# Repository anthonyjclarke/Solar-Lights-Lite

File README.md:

# Solar Lights Lite

Solar Lights Lite is a modular, low-power solar lighting system you build
yourself from common hobby modules. A small panel charges a protected Li-ion
battery; an ATmega328P controller sleeps most of the time, detects dusk with a
light sensor, and runs a **low-power LED string** from dusk to dawn. An
optional Wemos D1 Mini reports everything to Home Assistant.

It is also a learning project. Each module – power, controller, lighting,
sensor, telemetry – is built and tested on its own, so along the way you
practise soldering and SMD rework, read datasheets, program an AVR over ISP,
write low-power embedded C++, parse a serial protocol in ESPHome, and build
Home Assistant dashboards and automations.

---

## Low-power lights only

The controller drives the LED string **directly by PWM from pin D9** through a
56 Ω resistor. There is no driver transistor, so the whole string must run at
20 mA or less from a 3–4.2 V supply. Small low-power LED strings are ideal;
mains lights, 12 V garden lights and conventional or legacy fittings cannot be
used. The resistor sets the current and PWM sets the brightness. Brighter
lighting needs a driver stage: see [Going further](docs/12-going-further.md).

---

## System at a glance

```mermaid
flowchart LR
    PV[Solar panel] --> CHG[Protected Li-ion charger]
    CHG --> BAT[1S2P 18650 battery]
    CHG --> MCU[ATmega328P controller]
    MCU --> LDR[Light sensor]
    MCU -- PWM --> LED[Low-power LED string]
    MCU -. serial .-> D1[D1 Mini telemetry]
    D1 -. Wi-Fi .-> HA[Home Assistant]
```

| Module | What it does                       | Build guide                               |
| :----- | :--------------------------------- | :---------------------------------------- |
| A      | Panel, charger, fused 1S2P battery | [Power](docs/03-build-power.md)           |
| B      | ATmega328P controller at 8 MHz     | [Controller](docs/04-build-controller.md) |
| C      | Low-power LED string on D9         | [Lighting](docs/05-build-lighting.md)     |
| D      | Light sensor and test button       | [Sensor](docs/06-build-sensor.md)         |
| E      | D1 Mini telemetry (optional)       | [Telemetry](docs/07-build-telemetry.md)   |
| F      | Enclosure and final assembly       | [Commissioning](docs/10-commissioning.md) |

### Telemetry tiers

| Tier | Name                 | Role                               |
| :--- | :------------------- | :--------------------------------- |
| 0    | Standalone           | Lights only, no Wi-Fi              |
| 1    | Advanced Telemetry   | Always-on commissioning instrument |
| 2    | Production Telemetry | Hourly battery-powered reporting   |

**Advanced Telemetry is the road to a finished installation.** While you build,
calibrate and soak-test, it shows every decision the controller makes in Home
Assistant. When the system passes its acceptance gates, you reflash both boards
and move the D1 Mini to battery power for low-power production reporting. The
wiring stays the same.

---

## What you need

- The parts for each module: [parts, tools, skills and safety](docs/02-parts-and-tools.md)
  and the checklist [`docs/parts-list.csv`](docs/parts-list.csv).
- A soldering iron, a multimeter and a **current-limited bench supply**.
- A USBasp programmer (or a spare Arduino Uno/Nano as ISP).
- A computer with [PlatformIO](https://platformio.org/) and a standalone
  [avrdude](https://github.com/avrdudes/avrdude) 7.x.
- For telemetry: Home Assistant with ESPHome.

---

## Build path

The docs are organised by module; build in this order, passing each
commissioning gate before moving on:

1. Read the [design overview](docs/01-design-overview.md), including the
   known limitations.
2. Prepare the controller, set its fuses and flash the `advanced` firmware:
   [controller](docs/04-build-controller.md), [firmware](docs/08-firmware.md).
3. Add the [LED string](docs/05-build-lighting.md) and the
   [sensor and button](docs/06-build-sensor.md); pass Gates 1, 3 and 4 on a
   bench supply.
4. Build and qualify the [power module](docs/03-build-power.md): Gates 2, 5
   and 6.
5. Add [telemetry hardware](docs/07-build-telemetry.md) and set up
   [Home Assistant](docs/09-home-assistant.md) in Tier 1.
   To skip the perfboard, assemble the [PCB carrier](docs/13-pcb-carrier.md)
   instead and plug the modules into it.
6. Assemble the enclosure and run the 14-day soak (Gate 7), then switch to
   production (Gate 8): [commissioning](docs/10-commissioning.md).
7. Live with it: [operation and maintenance](docs/11-operation.md).

For a visual review of everything on one page – every guide with its drawings
inline, plus the wire schedule and parts checklist – open
[`docs/ASSEMBLY.html`](docs/ASSEMBLY.html) in a browser (download or clone the
repository first; GitHub shows HTML as source). Printable A3 drawings for every
module are in
[`docs/drawings/SolarLights_Lite_Drawings.pdf`](docs/drawings/SolarLights_Lite_Drawings.pdf).

---

## Repository map

| Path                   | Contents                                      |
| :--------------------- | :-------------------------------------------- |
| `docs/`                | Guides 01–13 and the one-page `ASSEMBLY.html` |
| `docs/drawings/`       | A3 sheets, pin map, USBasp and bench sheets   |
| `docs/images/pcb/`     | Rendered views of the PCB carrier             |
| `docs/reference/`      | Board photos, datasheet, LED characterisation |
| `firmware/controller/` | ATmega328P firmware and host tests            |
| `firmware/esphome/`    | D1 Mini profiles: Advanced and Production     |
| `homeassistant/`       | HA package and dashboards                     |
| `hardware/kicad/`      | KiCad schematic of the complete system        |
| `hardware/pcb-rev-c/`  | PCB carrier Rev C: current design, Gerbers    |
| `hardware/pcb-rev-b/`  | PCB carrier Rev B: as ordered (superseded)    |
| `hardware/pcb-rev-a/`  | Earlier, larger carrier (reference only)      |
| `tools/`               | Drawing and wiring-data generators            |

---

## Status

Version 0.6.0 is a complete build and operate package. The reference system is
built and running with Advanced Telemetry. The remaining steps before 1.0
are: removing the regulator and power LED from the bench controller board
([guide 04, step 5](docs/04-build-controller.md#5-remove-them)), which is
deferred to the production build; the 14-day soak; charger and panel
qualification; and the Tier 2 switch-over (Gates 5–8). See [`CHANGELOG.md`](CHANGELOG.md).

This is a hobby design, not a certified product. Read the
[safety notes](docs/02-parts-and-tools.md#safety) and the
[known limitations](docs/01-design-overview.md#known-limitations) before
leaving it unattended outdoors.

---

## Why build it?

This project started with a drawer of solar panels, light strings, charger
modules and microcontroller boards bought for projects that never quite
happened. Rather than buy another ready-made solar light, the aim was to put
those parts back to work, and to understand every part of the result: why a
charger needs its current set, why a microcontroller should run at 8 MHz on a
lithium cell, how little current a well-sleeping circuit can draw, and how to
watch it all from Home Assistant. AI assistants helped along the way as a
second opinion and a patient explainer.

Could it be cheaper, simpler, or less engineered? Almost certainly. But it is
a good excuse to learn, and good fun to build.

---

## Licence

Solar Lights Lite is dedicated to the public domain under
[CC0 1.0](LICENSE): firmware, ESPHome and Home Assistant configuration, tools,
documentation, drawings and schematics. Copy, modify, build and share it for
any purpose, without asking and without attribution.

The one exception is the third-party TPS63802 datasheet in `docs/reference/`,
which remains the property of its publisher and is included for reference.

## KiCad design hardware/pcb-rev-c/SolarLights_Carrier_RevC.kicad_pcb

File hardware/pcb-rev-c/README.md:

# Solar Lights Lite – PCB carrier Rev C

Started **28-Oct-2026** from Rev B. Status: **current design; CAD checks pass and fabrication files are exported, not yet ordered. Supplier DFM has not been run.**

Rev C started as a copy of the Rev B layout. [Guide 13](../../docs/13-pcb-carrier.md) describes how to
order, build and test it. The [Rev B README](../pcb-rev-b/README.md) still covers anything not changed
below: tiers, modules, TP4056 geometry and the open measurements.

Open `SolarLights_Carrier_RevC.kicad_pro` in **KiCad 10 or later**.

---

## What changed from Rev B

| Change         | Rev C                                         |
|:---------------|:----------------------------------------------|
| R3 LED feed    | 56 Ω (was 47 Ω): model 19.1 mA peak at 4.2 V  |
| LDR trim       | R4 22 kΩ + RV1 50 kΩ 3296W rheostat           |
| Test button    | On-board 6 × 6 mm tactile SW1 (was pads)      |
| ISP header     | Lies sideways below the Pro Mini; box outline |
| ISP option     | DC3-6P shrouded box header, keyed (optional)  |
| Silkscreen     | Name; GitHub repository up right edge         |
| Bottom row     | LED 17.2, LDR 22.3, U3 IN 36.9, U3 OUT 42.9 mm |
| C3, H1         | C3 to (20.0, 39.0); H1 to (3.5, 48.0) mm      |

**LDR trim.** R4 and RV1 form the lower leg of the LDR divider on A1. RV1 is wired as a rheostat
(wiper joined to pin 3), so the leg runs from 22 kΩ to 72 kΩ, and mid-travel gives the 47 kΩ that
`config.h` assumes. More resistance raises A1, so the lights wait for a darker dusk; less makes them
come on earlier. With the firmware's 0.30 dark ratio, the dusk point moves between an LDR of about
51 kΩ and 168 kΩ, with no reflash. Set RV1 to mid-travel (about 25 kΩ, pin 1 to pin 2) before
fitting. Which way of turning the screw adds resistance has not been checked on the part: confirm
with a meter.

**Button.** SW1 is a 4-pin through-hole 6 × 6 mm tactile switch (tall stem, about 9.5 mm) between
the LDR pads and U3 IN, clear of both modules. It replaces the remote-button solder pads.

**ISP.** `JISP1` now uses KiCad's `IDC-Header_2x03_P2.54mm_Vertical` footprint and lies on its side
below the Pro Mini. Pin 1 is at the lower left, odd pins are along the lower row, and the
silkscreen draws the outline of a DC3-6P box header with its key slot facing the bottom edge. The
outline starts about 0.7 mm below the Pro Mini outline. Fit either a plain 2 × 3 male header or,
optionally, the DC3-6P straight box header (2.54 mm, listed in the BOM as `JISP1 (option)`). The
box keys a 6-pin IDC cable so it cannot go on backwards. The box covers the space beside the pins,
so the pin names are a legend underneath it (`1 MISO 2 VCC / 3 SCK 4 MOSI / 5 RST 6 GND`). Check
that the box's key slot lines up with the cable's key before soldering.

---

## Working on Rev C

The board, schematic, footprints and BOM are generated from `tools/design.py` (placement, nets,
labels) and `tools/footprints.py`. Make layout changes there, not in KiCad, then rerun the checks;
`generate.py` overwrites the KiCad files. `tools/validate.py` holds the design rules (B– isolation,
board area, tier population): update it when a change is deliberate.

```
tools/run_checks.sh          # generate, polish, ERC, netlist, DRC with parity, validate
```

When the checks pass, `REPORTLAB_PY=<python with reportlab, pypdfium2> tools/build_outputs.sh` exports
the fabrication files, review PDFs, fit sheet and design zip. The renders go to `review/renders/`; copy
them to `docs/images/pcb/` for guide 13, then rerun `tools/make_guide.py` from the repository root.

Rev B stays unchanged as the record of the ordered board.

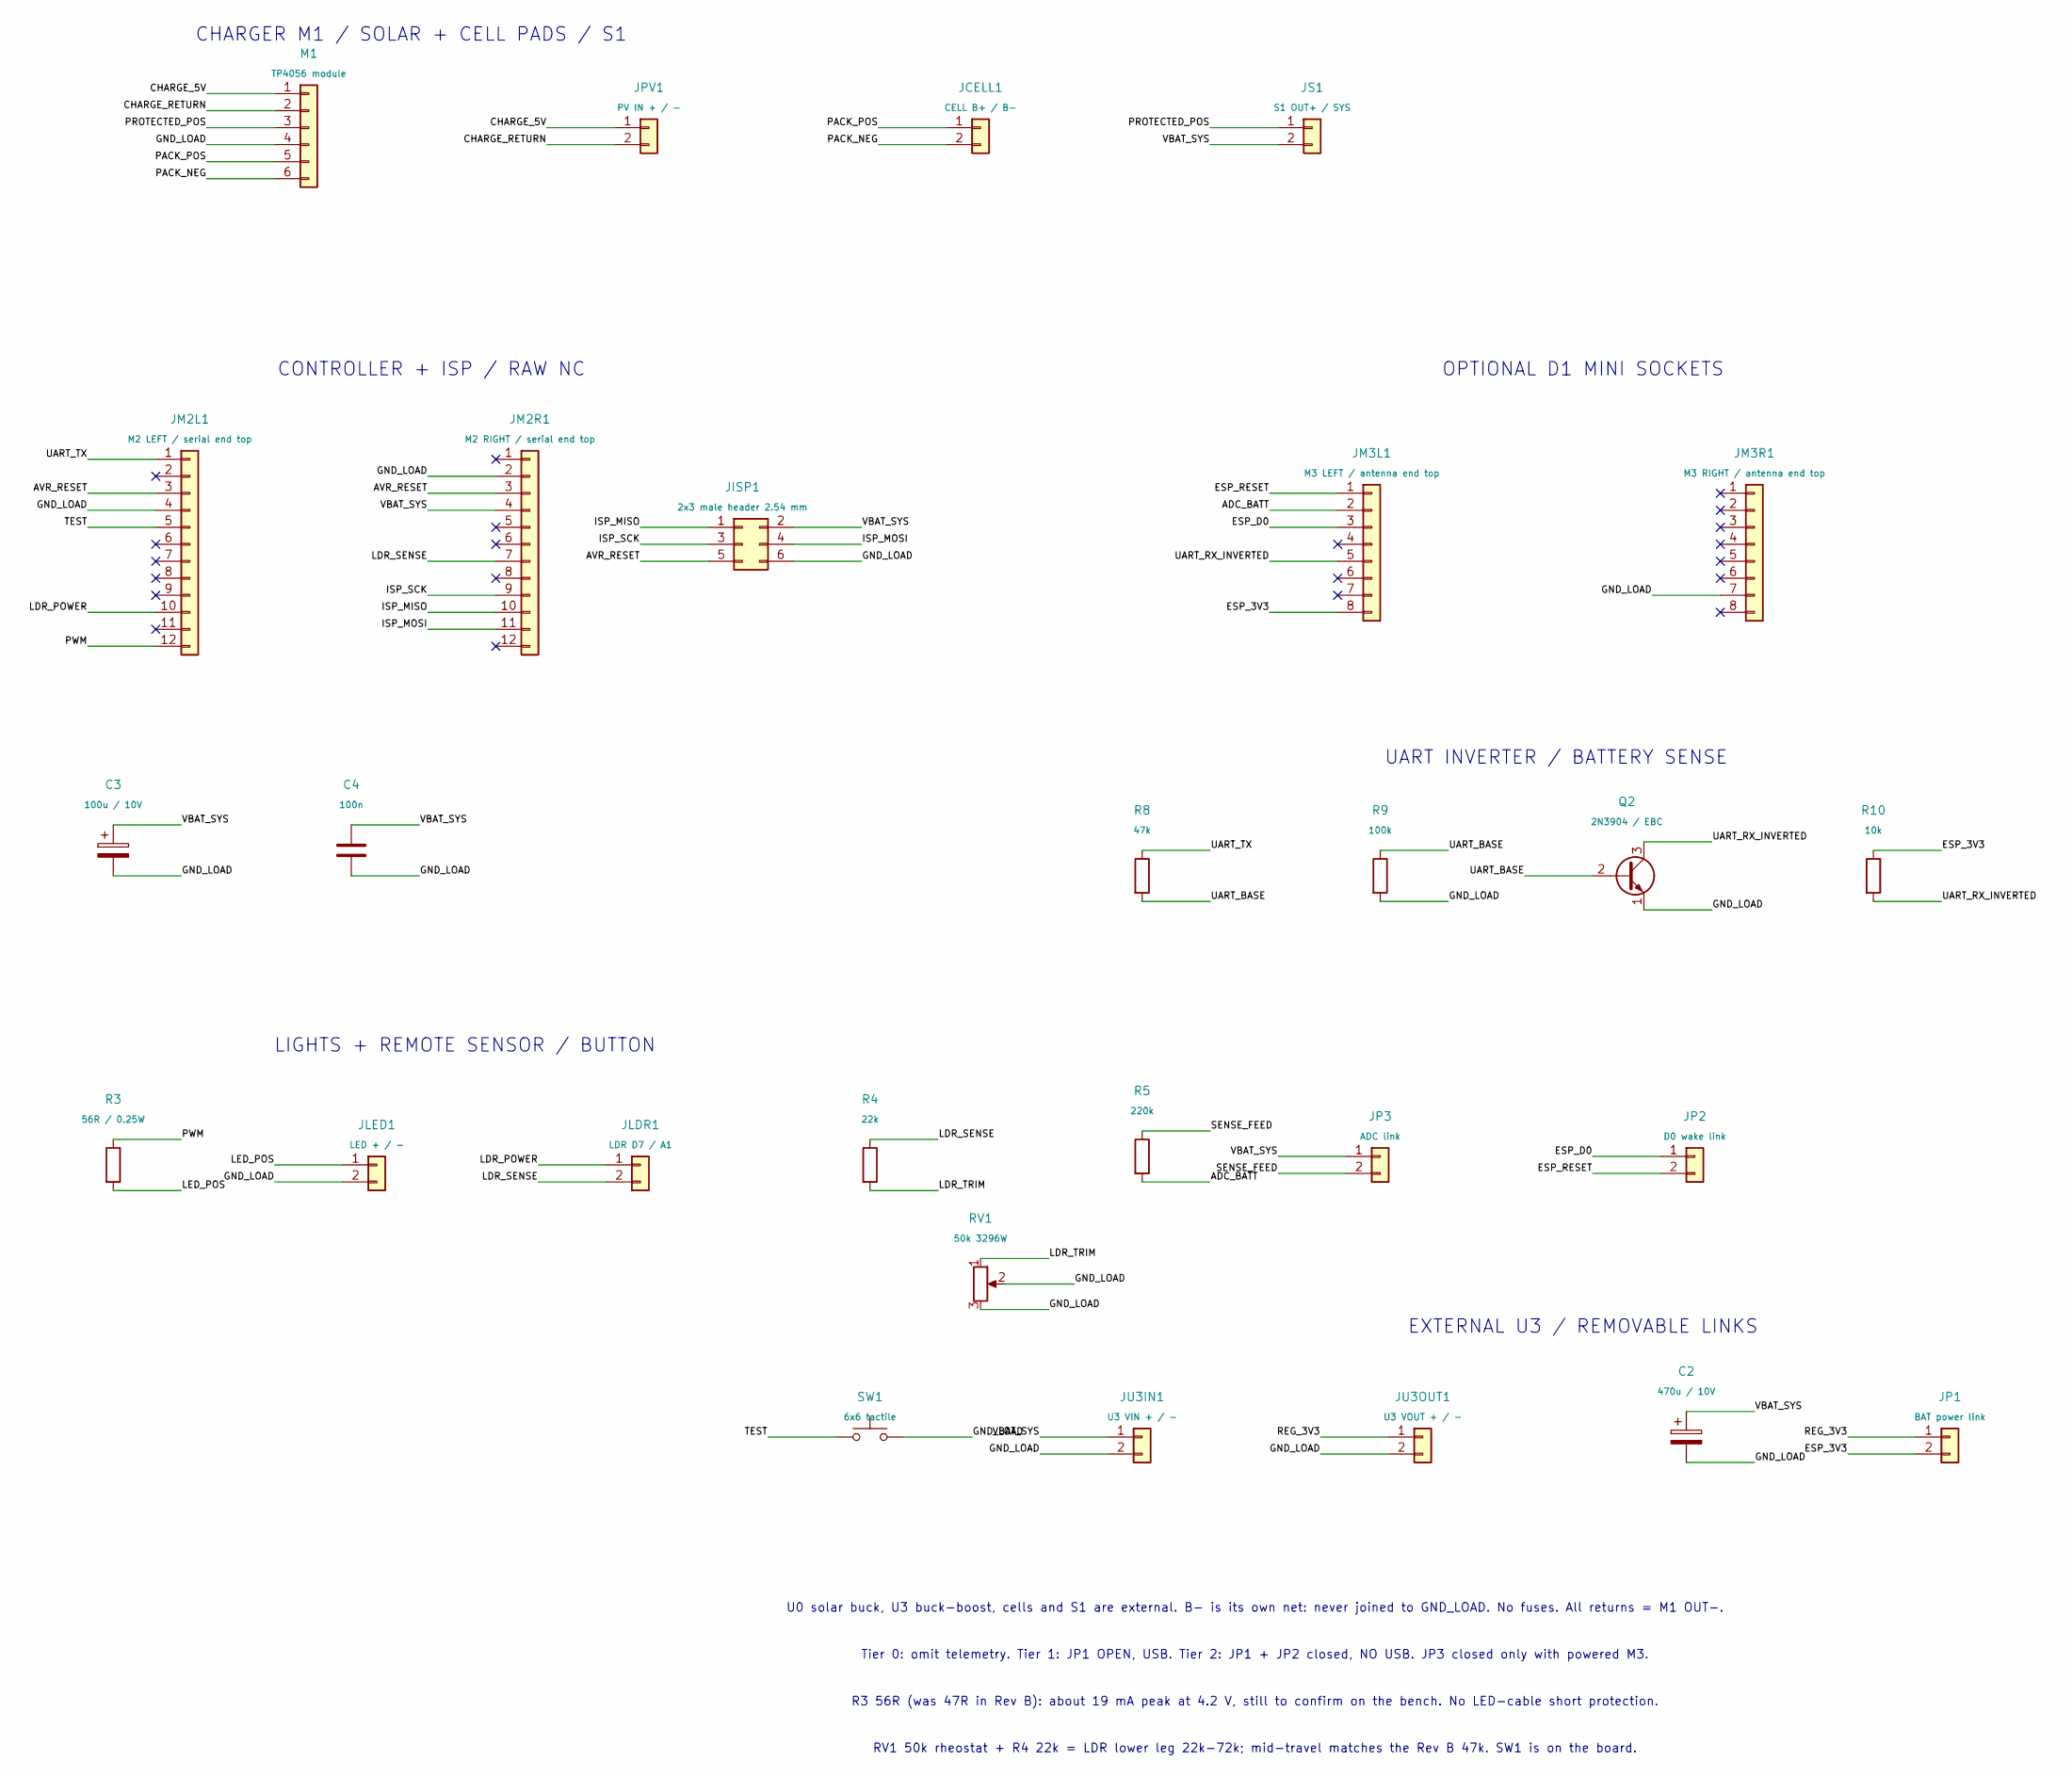
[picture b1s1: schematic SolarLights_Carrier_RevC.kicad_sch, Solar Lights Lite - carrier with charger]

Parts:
C2: 470u / 10V; CP_Radial_D10.0mm_P5.00mm
C3: 100u / 10V; CP_Radial_D6.3mm_P2.50mm
C4: 100n; C_Disc_D5.0mm_W2.5mm_P5.00mm
JCELL1: CELL B+ / B-; SolderPads_1x02_P2.54mm
JISP1: 2x3 male header 2.54 mm; IDC-Header_2x03_P2.54mm_Vertical
JLDR1: LDR D7 / A1; SolderPads_1x02_P2.54mm
JLED1: LED + / -; SolderPads_1x02_P2.54mm
JM2L1: M2 LEFT / serial end top; PinSocket_1x12_P2.54mm_Vertical
JM2R1: M2 RIGHT / serial end top; PinSocket_1x12_P2.54mm_Vertical
JM3L1: M3 LEFT / antenna end top; PinSocket_1x08_P2.54mm_Vertical
JM3R1: M3 RIGHT / antenna end top; PinSocket_1x08_P2.54mm_Vertical
JP1: BAT power link; SolderPads_1x02_P2.54mm
JP2: D0 wake link; SolderPads_1x02_P2.54mm
JP3: ADC link; SolderPads_1x02_P2.54mm
JPV1: PV IN + / -; SolderPads_1x02_P2.54mm
JS1: S1 OUT+ / SYS; SolderPads_1x02_P2.54mm
JU3IN1: U3 VIN + / -; SolderPads_1x02_P2.54mm
JU3OUT1: U3 VOUT + / -; SolderPads_1x02_P2.54mm
M1: TP4056 module; TP4056_Module_6pad_Overlay
Q2: 2N3904 / EBC; TO-92_Inline_Wide
R3: 56R / 0.25W; R_Axial_DIN0207_L6.3mm_D2.5mm_P7.62mm_Horizontal
R4: 22k; R_Axial_DIN0207_L6.3mm_D2.5mm_P7.62mm_Horizontal
R5: 220k; R_Axial_DIN0207_L6.3mm_D2.5mm_P7.62mm_Horizontal
R8: 47k; R_Axial_DIN0207_L6.3mm_D2.5mm_P7.62mm_Horizontal
R9: 100k; R_Axial_DIN0207_L6.3mm_D2.5mm_P7.62mm_Horizontal
R10: 10k; R_Axial_DIN0207_L6.3mm_D2.5mm_P7.62mm_Horizontal
RV1: 50k 3296W; Potentiometer_Bourns_3296W_Vertical
SW1: 6x6 tactile; SW_PUSH_6mm_H9.5mm

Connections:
/ADC_BATT: JM3L1.2, R5.2
/AVR_RESET: JISP1.5, JM2L1.3, JM2R1.3
/CHARGE_5V: JPV1.1, M1.1
/CHARGE_RETURN: JPV1.2, M1.2
/ESP_3V3: JM3L1.8, JP1.2, R10.1
/ESP_D0: JM3L1.3, JP2.1
/ESP_RESET: JM3L1.1, JP2.2
/GND_LOAD: C2.2, C3.2, C4.2, JISP1.6, JLED1.2, JM2L1.4, JM2R1.2, JM3R1.7, JU3IN1.2, JU3OUT1.2, M1.4, Q2.1 (E), R9.2, RV1.2, RV1.3, SW1.2
/ISP_MISO: JISP1.1, JM2R1.10
/ISP_MOSI: JISP1.4, JM2R1.11
/ISP_SCK: JISP1.3, JM2R1.9
/LDR_POWER: JLDR1.1, JM2L1.10
/LDR_SENSE: JLDR1.2, JM2R1.7, R4.1
/LDR_TRIM: R4.2, RV1.1
/LED_POS: JLED1.1, R3.2
/PACK_NEG: JCELL1.2, M1.6
/PACK_POS: JCELL1.1, M1.5
/PROTECTED_POS: JS1.1, M1.3
/PWM: JM2L1.12, R3.1
/REG_3V3: JP1.1, JU3OUT1.1
/SENSE_FEED: JP3.2, R5.1
/TEST: JM2L1.5, SW1.1
/UART_BASE: Q2.2 (B), R8.2, R9.1
/UART_RX_INVERTED: JM3L1.5, Q2.3 (C), R10.2
/UART_TX: JM2L1.1, R8.1
/VBAT_SYS: C2.1, C3.1, C4.1, JISP1.2, JM2R1.4, JP3.1, JS1.2, JU3IN1.1

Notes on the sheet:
CHARGER M1 / SOLAR + CELL PADS / S1
CONTROLLER + ISP / RAW NC
LIGHTS + REMOTE SENSOR / BUTTON
OPTIONAL D1 MINI SOCKETS
UART INVERTER / BATTERY SENSE
EXTERNAL U3 / REMOVABLE LINKS
U0 solar buck, U3 buck-boost, cells and S1 are external. B- is its own net: never joined to GND_LOAD. No fuses. All returns = M1 OUT-.
Tier 0: omit telemetry. Tier 1: JP1 OPEN, USB. Tier 2: JP1 + JP2 closed, NO USB. JP3 closed only with powered M3.
R3 56R (was 47R in Rev B): about 19 mA peak at 4.2 V, still to confirm on the bench. No LED-cable short protection.
RV1 50k rheostat + R4 22k = LDR lower leg 22k-72k; mid-travel matches the Rev B 47k. SW1 is on the board.

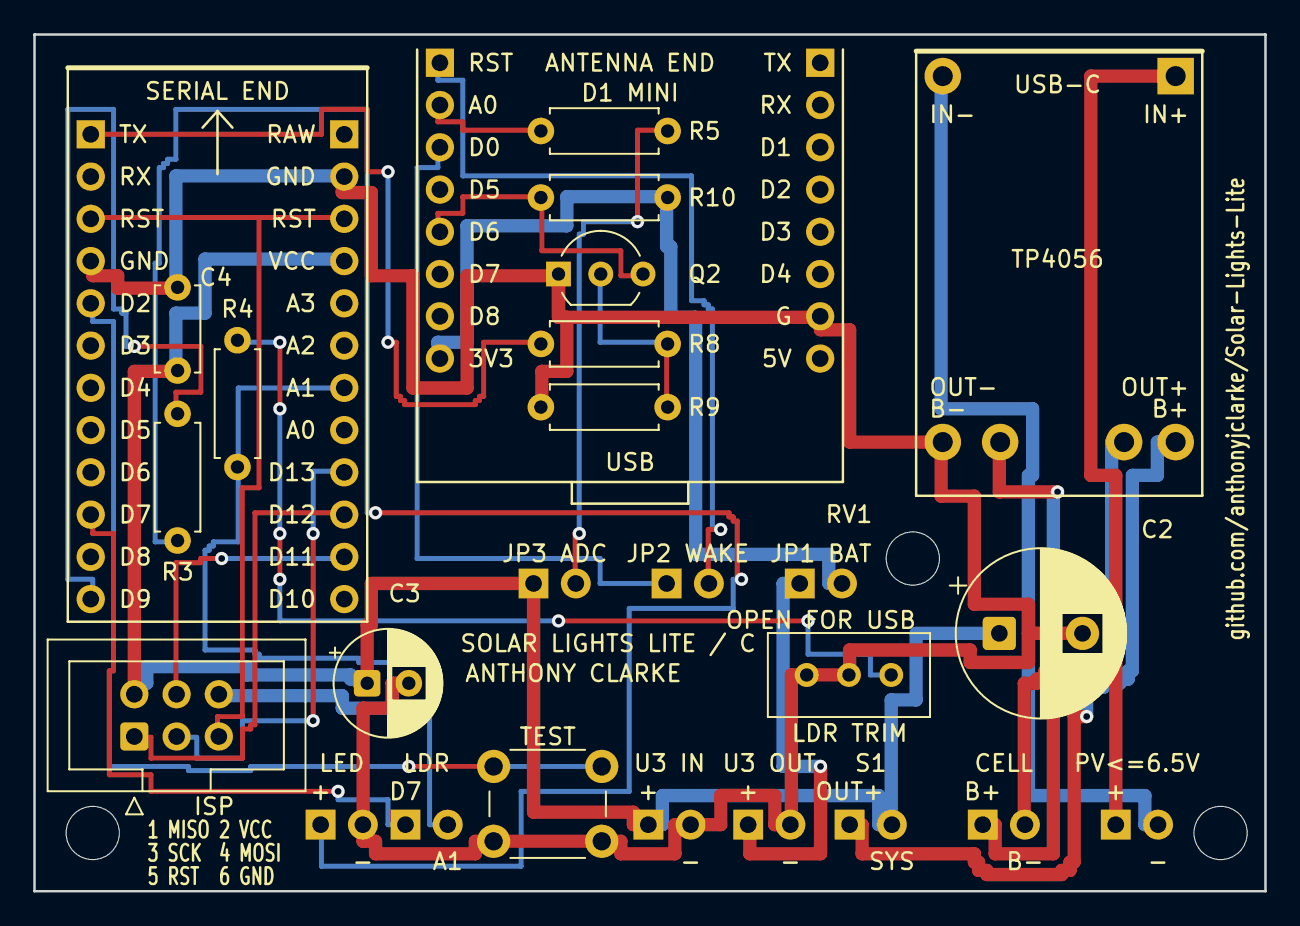
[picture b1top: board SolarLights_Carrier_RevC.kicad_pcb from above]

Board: 2 copper layers, 74.0 x 51.5 mm, 31 parts (0 on the bottom side), 26 nets.

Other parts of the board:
H1, H2, H3: MountingHole_3.2mm_Small

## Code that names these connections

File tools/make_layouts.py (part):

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    bb.add('R3', 'res', 37, 9, 0, ohms=56, label='R3 56R', lab=(39.8, 10.45, 'middle'))
    bb.add('R4', 'res', 38, 8, 0, span=6, ohms=22000, label='R4 22k', lab=(41, 7.35, 'middle'))
    bb.add('RV1', 'pot', 44, 10, 0, label='RV1 50k trim', lab=(47.6, 10.1, 'start'))
    bb.add('JP1', 'jumper', 15, 9, 0, nets=['ESP_3V3', 'ESP_3V3'], label='JP1', lab=(15.5, 7.75, 'middle'))

    # ---- jumper wires (breadboard wires carry the colour of their net)
    wires = [
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    ext['SPLICE-'] = (478, 214)
    cable('PV_POS', ('ext', 'PV1.+'), ('free', pin(u0, 'IN+')))
    cable('PV_RETURN', ('ext', 'PV1.-'), ('free', pin(u0, 'IN-')))
    cable('CHARGE_5V', ('free', pin(u0, 'OUT+')), ('free', pin(m1, 'IN+')))
    cable('CHARGE_RETURN', ('free', pin(u0, 'OUT-')), ('free', pin(m1, 'IN-')))
    cable('CELL1_POS', ('ext', 'BT1.+'), ('ext', 'FB1.1'), pts=[(198, 392), (362, 392), (362, 318)])
    cable('CELL2_POS', ('ext', 'BT2.+'), ('ext', 'FB2.1'), pts=[(282, 374), (350, 374), (350, 264)])
    cable('PACK_POS', ('ext', 'FB1.2'), ('ext', 'SPLICE+'))
    cable('PACK_POS', ('ext', 'FB2.2'), ('ext', 'SPLICE+'))
    cable('PACK_POS', ('ext', 'SPLICE+'), ('free', pin(m1, 'B+')))
    cable('PACK_NEG', ('ext', 'BT1.-'), ('ext', 'SPLICE-'), pts=[(198, 160), (240, 160), (300, 206)])
    cable('PACK_NEG', ('ext', 'BT2.-'), ('ext', 'SPLICE-'), pts=[(282, 164), (360, 164), (400, 214)])
    cable('PACK_NEG', ('ext', 'SPLICE-'), ('free', pin(m1, 'B-')))
    cable('PROTECTED_POS', ('free', pin(m1, 'OUT+')), ('ext', 'F2.1'))
    cable('FUSED_POS', ('ext', 'F2.2'), ('ext', 'S1.1'))
    cable('VBAT_SYS', ('ext', 'S1.2'), hole((22, -4)))
    cable('GND_LOAD', ('free', pin(m1, 'OUT-')), hole((3, -3)), pts=[(520, 142), (100, 142), (100, 490), (194, 490)])
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    add('R10', 'res', 18, 7, 270, span=3, ohms=10000, label='R10 10k', lab=(17.5, 5.9, 'end'))
    add('JP2', 'jumper', 14, 0, 90, nets=['WAKE:d0', 'WAKE:rst'], label='JP2', lab=(14, -0.95, 'middle'))
    add('R5', 'res', 18, 2, 180, ohms=220000, label='R5 220k', lab=(16, 1.35, 'middle'))
    add('JP1', 'jumper', 16, 8, 0, nets=['ESP_3V3:u3', 'ESP_3V3'], label='JP1', lab=(15.3, 8.3, 'end'))
    add('U3', 'hl802', 14, 10, 0, label='U3 3.3 V', lab=(15.5, 9.2, 'middle'))
    add('C2', 'elec', 14, 14, 0, rad=1.2, pitch=2, label='C2 470u', lab=(17.4, 14.35, 'start'))
    add('R3', 'res', 27, 13, 90, span=3, ohms=56, label='R3 56R', lab=(26.4, 15.6, 'end'))
    add('J4', 'term', 37, 15, 90, nets=['GND_LOAD', 'LED_POS'], label='J4 LED', lab=(37.2, 19.1, 'middle'))
    add('J5', 'term', 37, 10, 90, nets=['LDR_SENSE', 'LDR_POWER'], label='J5 LDR', lab=(37.2, 8.75, 'middle'))
    add('M1', 'tp4056', 13, 22, 180, label='M1  protected TP4056', lab=(8, 16.35, 'middle'))
    add('U0', 'buck', 23, 22, 180, label='U0  5 V buck (Option B)', lab=(19.5, 16.35, 'middle'))
    add('J1', 'term', 24, 25, 180, nets=['PV_RETURN', 'PV_POS'], label='J1 PV', lab=(26, 24.3, 'start'))
    add('J2', 'term', 0, 21, 270, nets=['PACK_POS', 'PACK_NEG'], label='J2 BATT', lab=(-0.4, 17.4, 'middle'))
    add('J3', 'term', 5, 25, 180, nets=['VBAT_SYS', 'PROTECTED_POS'], label='J3 F2/S1', lab=(7, 24.3, 'start'))
    topwires = [((34, 5), (34, 18), 'VBAT_SYS')]
    override = {'M3.D0': 'WAKE:d0', 'M3.RST': 'WAKE:rst', 'U3.VOUT': 'ESP_3V3:u3'}

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                ex, ey = rot(0, -1.3, p.r)
                entry[xy] = pb.px(xy[0] + ex, xy[1] + ey)
    cables = [
        ('PACK_POS', ('pb', tpin['J2', 0]), ('ext', 'SPLICE+'), dict(pts=[(318, 784)])),
        ('PACK_NEG', ('pb', tpin['J2', 1]), ('ext', 'SPLICE-'), dict(pts=[(318, 728)])),
        ('PACK_POS', ('ext', 'FB2.2'), ('ext', 'SPLICE+'), dict(pts=[(318, 690)])),
        ('PACK_POS', ('ext', 'FB1.2'), ('ext', 'SPLICE+'), {}),
        ('CELL2_POS', ('ext', 'BT2.+'), ('ext', 'FB2.1'), dict(pts=[(162, 810), (220, 810), (220, 690)])),
        ('CELL1_POS', ('ext', 'BT1.+'), ('ext', 'FB1.1'), dict(pts=[(78, 830), (232, 830), (232, 742)])),
        ('PACK_NEG', ('ext', 'BT1.-'), ('ext', 'SPLICE-'), dict(pts=[(78, 584), (318, 584)])),
        ('PACK_NEG', ('ext', 'BT2.-'), ('ext', 'SPLICE-'), dict(pts=[(162, 598), (304, 598), (304, 640)])),
        ('PROTECTED_POS', ('pb', tpin['J3', 1]), ('ext', 'F2.1'), dict(pts=[(464, 972), (340, 972), (340, 1010)])),
        ('FUSED_POS', ('ext', 'F2.2'), ('ext', 'S1.1'), dict(pts=[(480, 1010), (480, 994)])),
        ('VBAT_SYS', ('ext', 'S1.2'), ('pb', tpin['J3', 0]), dict(pts=[(540, 1052), (600, 1052), (600, 962), (520, 962)])),
        ('PV_POS', ('ext', 'PV1.+'), ('pb', tpin['J1', 1]), dict(pts=[(996, 1051)])),
        ('PV_RETURN', ('ext', 'PV1.-'), ('pb', tpin['J1', 0]), dict(pts=[(1052, 1029)])),
        ('LDR_SENSE', ('pb', tpin['J5', 0]), ('ext', 'LDR1.2'), dict(pts=[(1654, 476)])),
        ('LDR_POWER', ('pb', tpin['J5', 1]), ('ext', 'LDR1.1'), dict(pts=[(1666, 532)])),
        ('GND_LOAD', ('pb', tpin['J4', 0]), ('ext', 'JLED.-'), dict(pts=[(1500, 616), (1500, 632)])),
        ('LED_POS', ('pb', tpin['J4', 1]), ('ext', 'JLED.+'), dict(pts=[(1512, 672), (1512, 648)])),
    ]
    for net, a, b, _ in cables:
        nets.join(pb.node(a[1]) if a[0] == 'pb' else a, pb.node(b[1]) if b[0] == 'pb' else b)
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

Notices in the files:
README.md:
licence: CC0 1.0
